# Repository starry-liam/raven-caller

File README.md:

# raven-caller
A pager system for FRC Competitions by team 5276

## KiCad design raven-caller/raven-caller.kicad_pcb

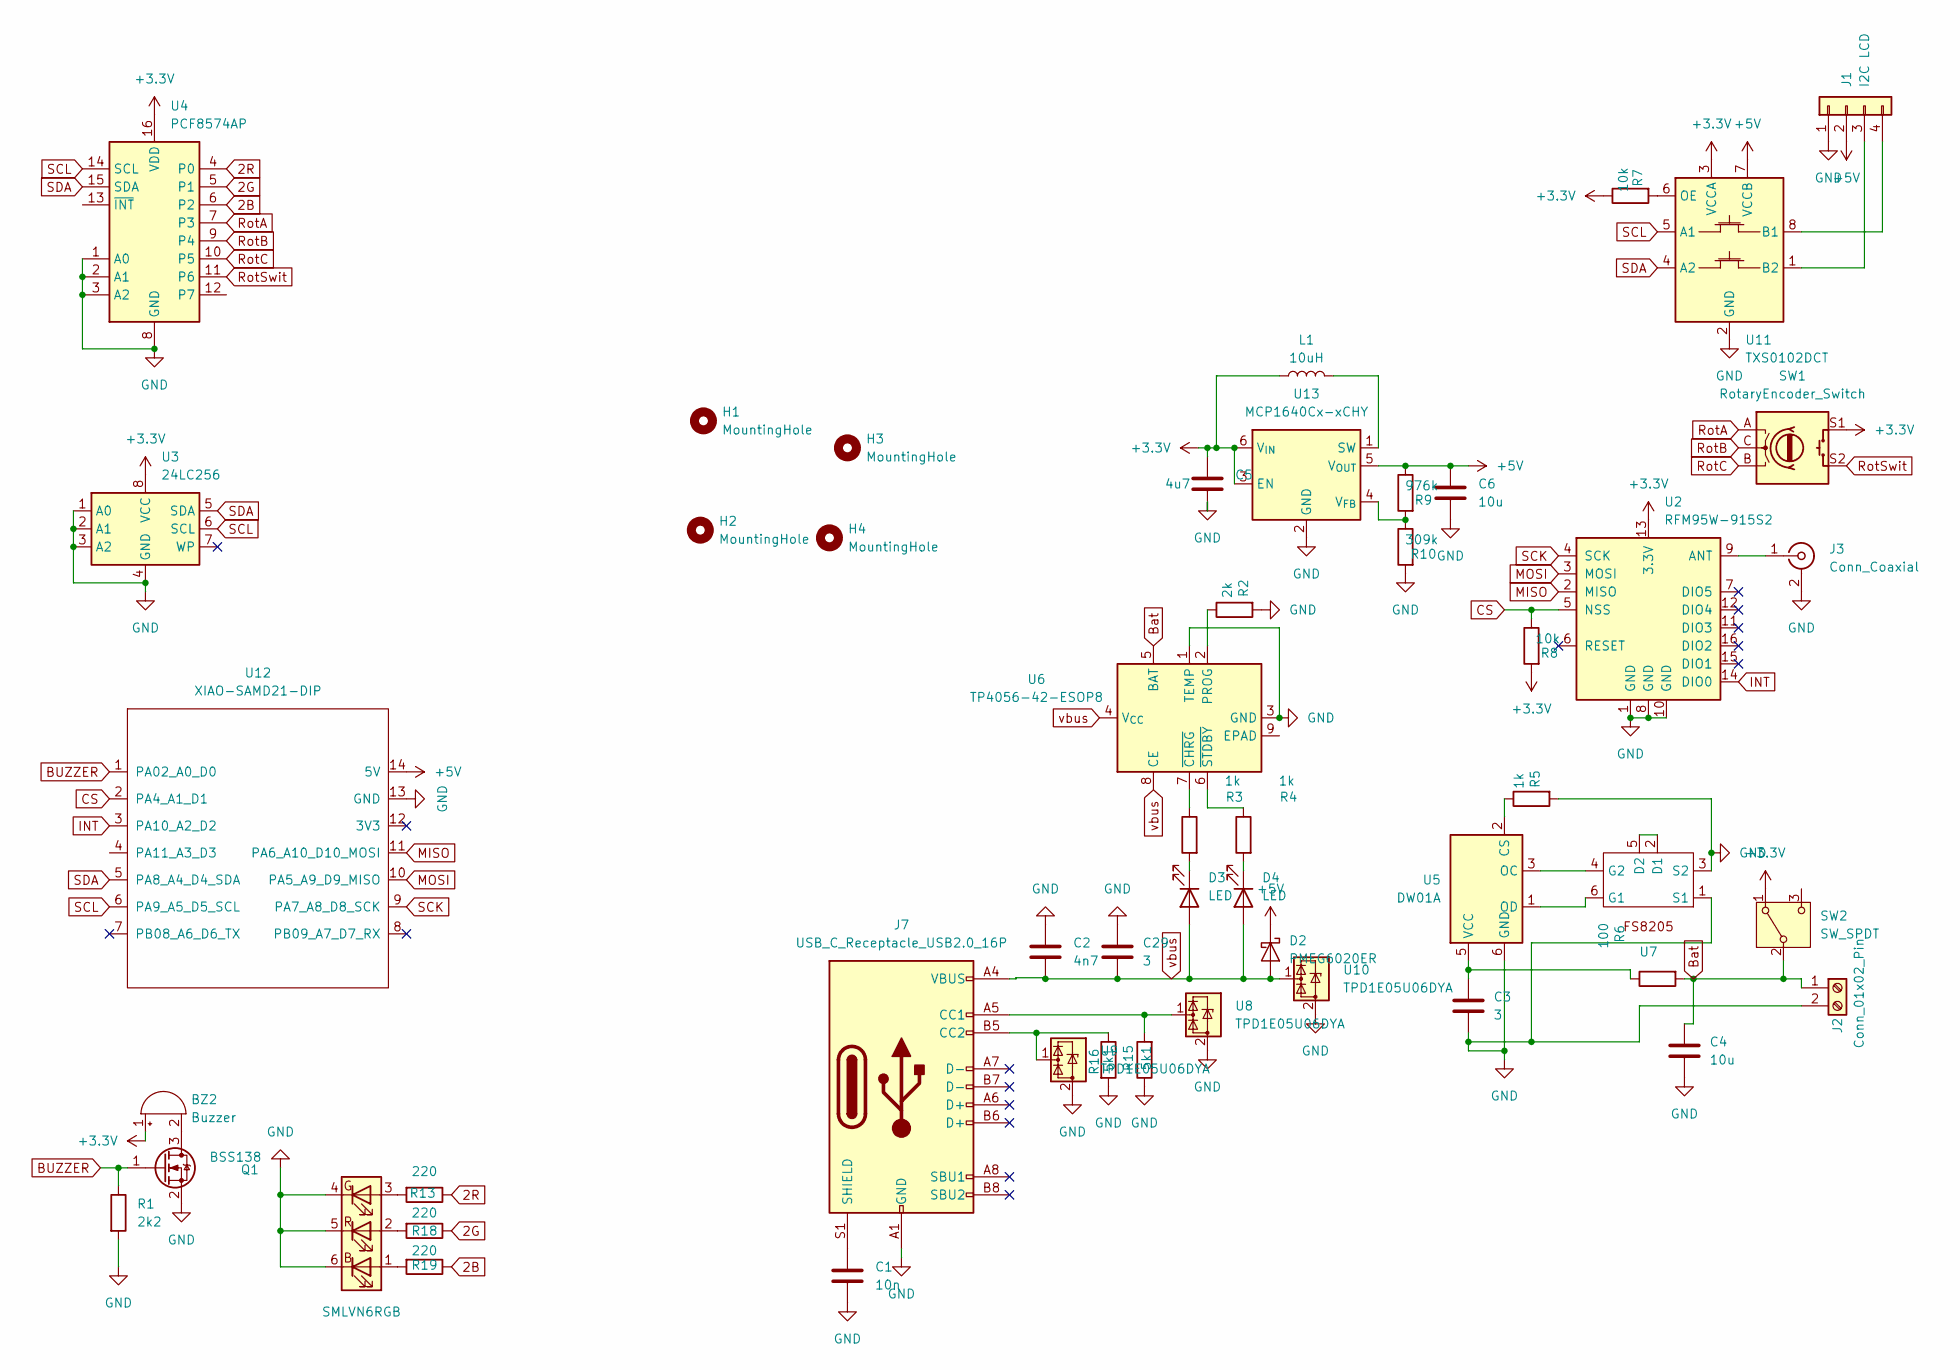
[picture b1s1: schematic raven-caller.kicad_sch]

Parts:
BZ2: Buzzer; MagneticBuzzer_PUI_AT-0927-TT-6-R
C1: 10n; C_0603_1608Metric
C2: 4n7; C_0603_1608Metric
C3, C29: 3; C_0603_1608Metric
C4, C6: 10u; C_0603_1608Metric
C5: 4u7; C_0603_1608Metric
D1: SMLVN6RGB; LED_ROHM_SMLVN6
D2: PMEG6020ER; Nexperia_CFP3_SOD-123W
D3, D4: LED; LED_0603_1608Metric
H1, H2, H3, H4: MountingHole; MountingHole_2.2mm_M2
J1: I2C LCD; PinHeader_1x04_P2.54mm_Horizontal
J2: Conn_01x02_Pin; JST_PH_B2B-PH-K_1x02_P2.00mm_Vertical
J3: Conn_Coaxial; U.FL_Molex_MCRF_73412-0110_Vertical
J7: USB_C_Receptacle_USB2.0_16P; USB_C_Receptacle_GCT_USB4105-xx-A_16P_TopMnt_Horizontal
L1: 10uH; L_6.3x6.3_H3
Q1: BSS138; SOT-23
R1: 2k2; R_0603_1608Metric
R2: 2k; R_0603_1608Metric
R3, R4, R5: 1k; R_0603_1608Metric
R6: 100; R_0603_1608Metric
R7, R8: 10k; R_0603_1608Metric
R9: 976k; R_0603_1608Metric
R10: 309k; R_0603_1608Metric
R13, R18, R19: 220; R_0603_1608Metric
R15, R16: 5k1; R_0603_1608Metric
SW1: RotaryEncoder_Switch; RotaryEncoder_Alps_EC11E-Switch_Vertical_H20mm
SW2: SW_SPDT; SW_Slide_SPDT_Angled_CK_OS102011MA1Q
U2: RFM95W-915S2; HOPERF_RFM9XW_SMD
U3: 24LC256; SOIC-8_3.9x4.9mm_P1.27mm
U4: PCF8574AP; DIP-16_W7.62mm
U5: DW01A; SOT-23-6
U6: TP4056-42-ESOP8; SOIC-8-1EP_3.9x4.9mm_P1.27mm_EP2.41x3.3mm_ThermalVias
U7: SOT-23-6
U8, U9, U10: TPD1E05U06DYA; D_SOD-523
U11: TXS0102DCT; SSOP-8_2.95x2.8mm_P0.65mm
U12: XIAO-SAMD21-DIP
U13: MCP1640Cx-xCHY; SOT-23-6

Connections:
2B: R19.1, U4.6 (P2)
2G: R18.1, U4.5 (P1)
2R: R13.1, U4.4 (P0)
+3.3V: BZ2.1 (+), C5.1, L1.1, R7.1, R8.2, SW1.S1, SW2.1 (A), U2.13 (3.3V), U3.8 (VCC), U4.16 (VDD), U11.3 (VCCA), U13.3 (EN), U13.6 (V_{IN})
+5V: C6.1, D2.1 (K), J1.2, R9.1, U11.7 (VCCB), U12.14 (5V), U13.5 (V_{OUT})
BUZZER: Q1.1 (G), R1.1, U12.1 (PA02_A0_D0)
Bat: C4.1, J2.1, R6.2, SW2.2 (B), U6.5 (BAT)
CS: R8.1, U2.5 (NSS), U12.2 (PA4_A1_D1)
GND: C1.2, C2.1, C3.2, C4.2, C5.2, C6.2, C29.1, D1.4 (GK), D1.5 (RK), D1.6 (BK), J1.1, J2.2, J3.2 (Ext), J7.A1 (GND), J7.A12 (GND), J7.B1 (GND), J7.B12 (GND), Q1.2 (S), R1.2, R2.2, R5.2, R10.2, R15.1, R16.2, U2.1 (GND), U2.8 (GND), U2.10 (GND), U3.1 (A0), U3.2 (A1), U3.3 (A2), U3.4 (GND), U4.1 (A0), U4.2 (A1), U4.3 (A2), U4.8 (GND), U5.6 (GND), U6.1 (TEMP), U6.3 (GND), U7.1 (S1), U7.3 (S2), U8.2 (GND), U9.2 (GND), U10.2 (GND), U11.2 (GND), U12.13 (GND), U13.2 (GND)
INT: U2.14 (DIO0), U12.3 (PA10_A2_D2)
MISO: U2.2 (MISO), U12.11 (PA6_A10_D10_MOSI)
MOSI: U2.3 (MOSI), U12.10 (PA5_A9_D9_MISO)
unnamed: BZ2.2 (-), Q1.3 (D)
unnamed: D1.1 (BA), R19.2
unnamed: D1.3 (GA), R13.2
unnamed: D1.2 (RA), R18.2
unnamed: D3.1 (K), R3.2
unnamed: D4.1 (K), R4.2
unnamed: J1.3, U11.1 (B2)
unnamed: J1.4, U11.8 (B1)
unnamed: J3.1 (In), U2.9 (ANT)
unnamed: J7.A5 (CC1), R15.2, U8.1 (I/O)
unnamed: J7.B5 (CC2), R16.1, U9.1 (I/O)
unnamed: C1.1, J7.S1 (SHIELD)
unnamed: R5.1, U5.2 (CS)
unnamed: U5.3 (OC), U7.4 (G2)
unnamed: U5.1 (OD), U7.6 (G1)
unnamed: C3.1, R6.1, U5.5 (VCC)
unnamed: R2.1, U6.2 (PROG)
unnamed: R3.1, U6.7 (~CHRG)
unnamed: R4.1, U6.6 (~STDBY)
unnamed: U7.2 (D1), U7.5 (D2)
unnamed: R7.2, U11.6 (OE)
unnamed: L1.2, U13.1 (SW)
unnamed: R9.2, R10.1, U13.4 (V_{FB})
RotA: SW1.A, U4.7 (P3)
RotB: SW1.C, U4.9 (P4)
RotC: SW1.B, U4.10 (P5)
RotSwit: SW1.S2, U4.11 (P6)
SCK: U2.4 (SCK), U12.9 (PA7_A8_D8_SCK)
SCL: U3.6 (SCL), U4.14 (SCL), U11.5 (A1), U12.6 (PA9_A5_D5_SCL)
SDA: U3.5 (SDA), U4.15 (SDA), U11.4 (A2), U12.5 (PA8_A4_D4_SDA)
vbus: C2.2, C29.2, D2.2 (A), D3.2 (A), D4.2 (A), J7.A4 (VBUS), J7.A9 (VBUS), J7.B4 (VBUS), J7.B9 (VBUS), U6.4 (V_{CC}), U6.8 (CE), U10.1 (I/O)

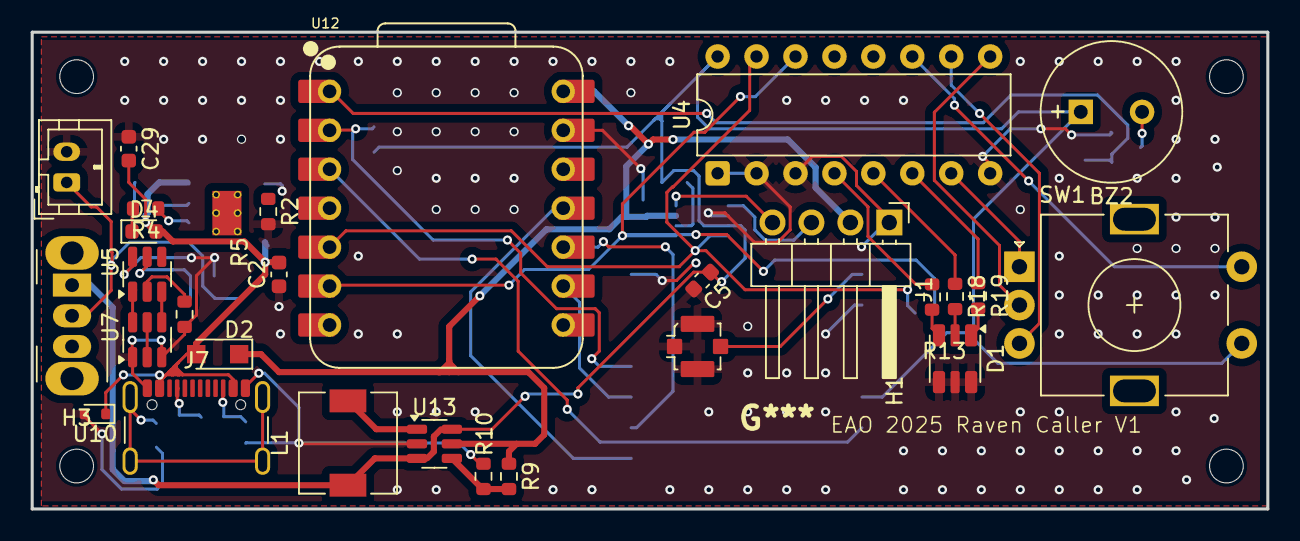
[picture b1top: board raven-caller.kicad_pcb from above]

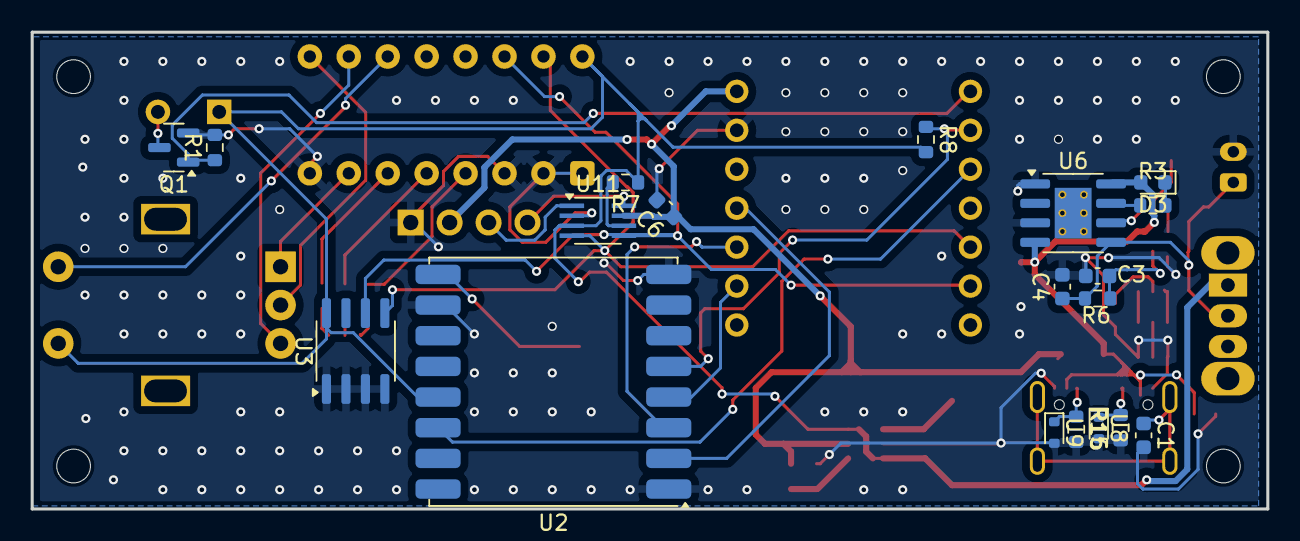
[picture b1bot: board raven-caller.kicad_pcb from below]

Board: 2 copper layers, 80.6 x 31.1 mm, 51 parts (19 on the bottom side), 43 nets.

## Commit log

2025-07-13 added parts to schematic
2025-07-14 schematic v1 done
2025-07-14 traces v1 done!
2025-07-14 routes v2 and "fixed" drc
2025-07-17 final pcb(i hope)
2025-07-18 final fixes
